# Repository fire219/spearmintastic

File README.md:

# Spearmintastic!
## Self-sufficient, pocket sized
**Spearmintastic** is a pocket-sized device designed for use as Meshtastic node. Unlike most other tiny node designs, it is designed to be fully self sufficient (including battery, solar panel, and LoRa antenna) in a footprint no larger than its 21x71mm PCB.

**Spearmintastic** uses a "14500" (AA) size protected Li-ion battery, minimizing fears about sketchy pouch cells from Amazon or AliExpress. These can be found via online retailers as "flashlight batteries".

## Errata Notes:

- Solar polarity silkscreen is reversed on v1.0 board
- Protected 14500 lithium cells tend to be a couple millimeters longer than a "normal" AA battery. You may need to do some modifications to the Keystone holder to make the battery fit well. If needed, recommended modifications are to flatten the contact springs with a pair of pliers, as well as cutting some of the plastic "backstop" out from behind the positive contact to allow it more travel.

## Bill Of Materials

| Part | Spec | Qty | Link |
|--|--|--|--|
| PCB | Spearmintastic v1.0 | 1 | This repository! |
| Microcontroller | Seeed Studio XIAO nRF52840 | 1 | [DigiKey](https://www.digikey.com/en/products/detail/seeed-technology-co-ltd/102010448/16652893) |
| LoRa Radio | Ai-Thinker Ra-01SH ***or*** Heltec HT-RA62 | 1 | [Ra-01SH](https://www.aliexpress.us/item/3256802374880132.html) or [HT-RA62](https://www.aliexpress.us/item/3256805259034353.html) |
| Solar Charger | SD05CRMA (CN3163 Breakout) | 1 | [AliExpress](https://www.aliexpress.us/item/3256805359874309.html) |
| Antenna | Pulse W3139 | 1 | [DigiKey](https://www.digikey.com/en/products/detail/pulse-electronics/W3139/9817201) |
| Solar Panel | ANYSOLAR SM141K09L | 1 | [DigiKey](https://www.digikey.com/en/products/detail/anysolar-ltd/SM141K09L/9990465) |
| Solar Panel Pigtail | 2x wire, 1.25mm PicoBlade termination | 1 | [DigiKey](https://www.digikey.com/en/products/detail/molex/0151340200/6198138) |
| Solar Panel Connector | 2 position 1.25mm PicoBlade, vertical THT | 1 | [DigiKey](https://www.digikey.com/en/products/detail/molex/0530470210/242853)
| Solar Overvoltage Shunt | 6.2V Zener Diode (SOD123 package) | 1 | [DigiKey](https://www.digikey.com/en/products/detail/micro-commercial-co/MMSZ4691-TP/2345540) |
| Bulk Capacitor | 10uF MLCC capacitor (1206 package) | 1 | [DigiKey](https://www.digikey.com/en/products/detail/samsung-electro-mechanics/CL31A106MAHNNNE/3886839) | 
| Battery Holder | Keystone 1024 *(see note)* | 1 | [DigiKey](https://www.digikey.com/en/products/detail/keystone-electronics/1024/2178268) |
| Battery | 14500 size Li-Ion cell (protected) | 1 | [B&H Photo](https://www.bhphotovideo.com/c/product/1811929-REG/nitecore_nl1410_14500_li_ion_rechargeable.html) |
| Case *(optional)* | Spearmintastic case | 1 | Your 3D printer (files on this repo)

## Case
A 3D printable case has been designed to fit a fully assembled Spearmintastic, with battery and panel. A cutout is provided for access to the Xiao's USB-C port.

## Firmware
*Pre-built firmware coming soon?*

Meshtastic built for the "xiao_ble" target should be directly compatible with Spearmintastic, however in my testing, the battery voltage indication does not work. This can be fixed by adding the following to the *variant.cpp* file:

    void initVariant() {
	    pinMode(BAT_READ, OUTPUT);
	    digitalWrite(BAT_READ, LOW);
    }
This is not an issue specific to Spearmintastic, as the voltage monitoring circuit is built onto the Xiao.

## License

**Spearmintastic** is licensed under the CERN OHL v2 Permissive license. See the *LICENSE* file for more information.

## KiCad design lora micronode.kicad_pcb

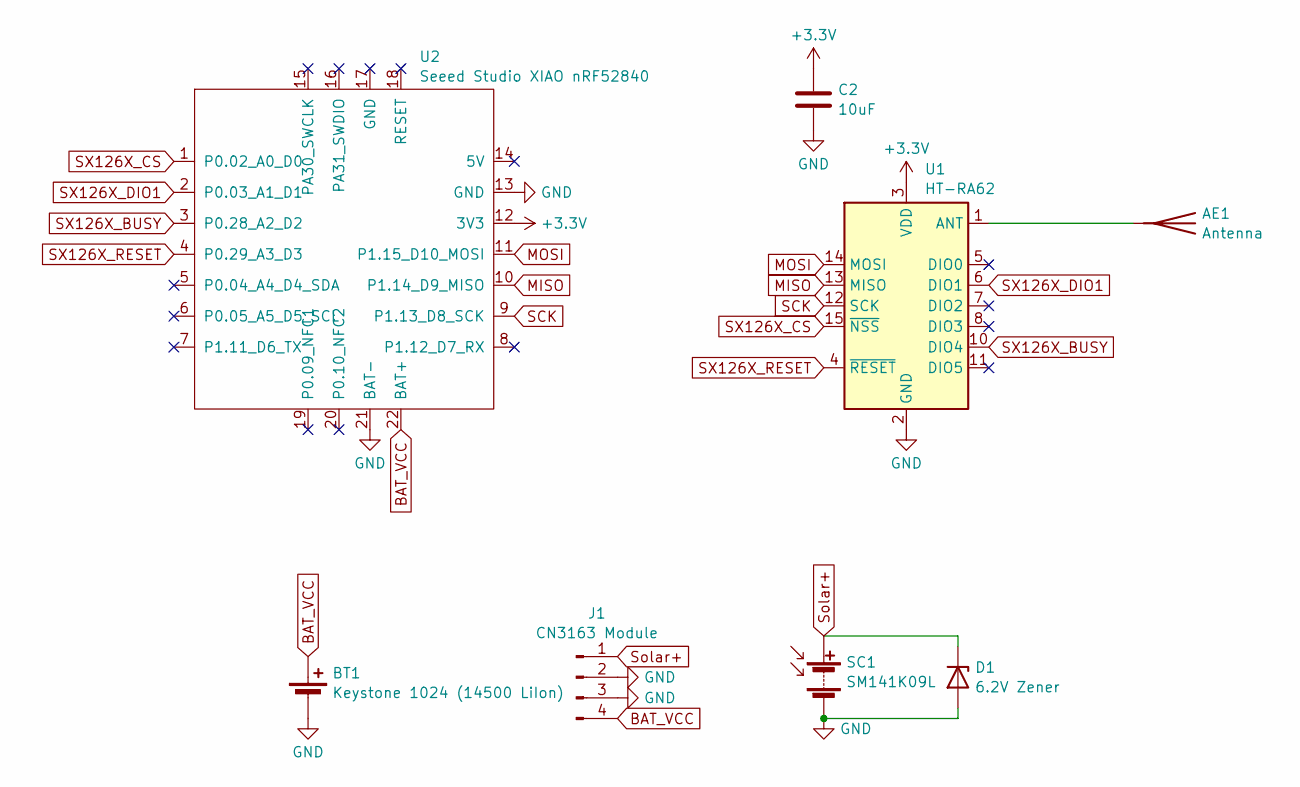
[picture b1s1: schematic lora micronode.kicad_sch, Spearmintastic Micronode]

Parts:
AE1: Antenna; 18mm-Antenna-THT
BT1: Keystone 1024 (14500 LiIon); Keystone_1024_SMD_14500
C2: 10uF; C_1206_3216Metric_Pad1.33x1.80mm_HandSolder
D1: 6.2V Zener; D_SOD-123F
J1: CN3163 Module; CN3163_Module
SC1: SM141K09L; Molex_PicoBlade_53047-0210_1x02_P1.25mm_Vertical
U1: HT-RA62; Ai-Thinker-Ra-01-LoRa
U2: Seeed Studio XIAO nRF52840; XIAO-nRF-THT_batt

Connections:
+3.3V: C2.1, U1.3 (VDD), U2.12 (3V3)
BAT_VCC: BT1.1 (+), J1.4, U2.22 (BAT+)
GND: BT1.2 (-), C2.2, D1.2 (A), J1.2, J1.3, SC1.2 (-), U1.2 (GND), U1.9 (GND), U1.16 (GND), U2.13 (GND), U2.21 (BAT-)
MISO: U1.13 (MISO), U2.10 (P1.14_D9_MISO)
MOSI: U1.14 (MOSI), U2.11 (P1.15_D10_MOSI)
unnamed: AE1.1 (A), U1.1 (ANT)
SCK: U1.12 (SCK), U2.9 (P1.13_D8_SCK)
SX126X_BUSY: U1.10 (DIO4), U2.3 (P0.28_A2_D2)
SX126X_CS: U1.15 (~NSS), U2.1 (P0.02_A0_D0)
SX126X_DIO1: U1.6 (DIO1), U2.2 (P0.03_A1_D1)
SX126X_RESET: U1.4 (~RESET), U2.4 (P0.29_A3_D3)
Solar+: D1.1 (K), J1.1, SC1.1 (+)

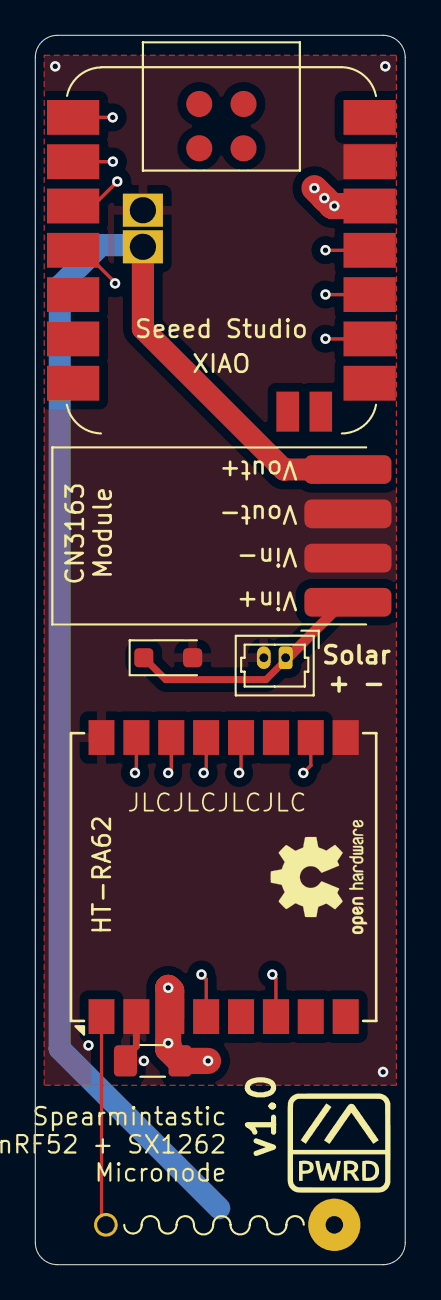
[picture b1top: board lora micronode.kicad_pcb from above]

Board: 4 copper layers, 21.2 x 70.5 mm, 9 parts (1 on the bottom side), 12 nets.

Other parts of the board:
.: LOGO; m_powered

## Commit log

2024-11-23 Initial GitHub release
2024-11-23 it helps if you save the README before push
2024-11-23 errata notes
2024-11-24 add second errata note
